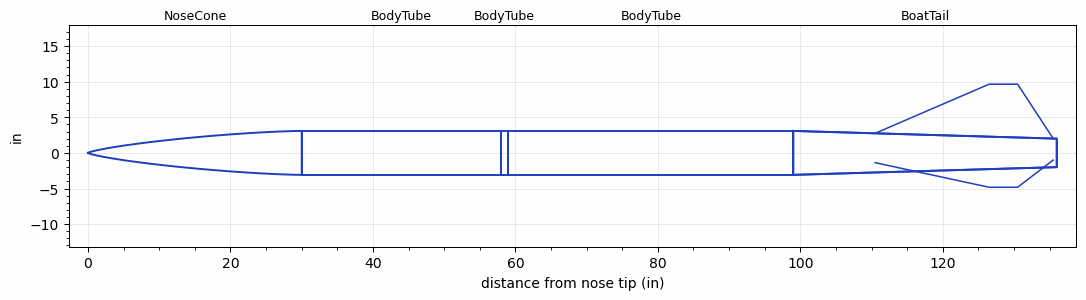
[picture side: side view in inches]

<RASAeroDocument>
 <FileVersion>2</FileVersion>
 <RocketDesign>
  <NoseCone>
   <Length>29.9999</Length>
   <Diameter>6.17</Diameter>
   <Shape>Von Karman Ogive</Shape>
   <Location>0</Location>
  </NoseCone>
  <BodyTube>
   <Length>27.9999</Length>
   <Diameter>6.17</Diameter>
   <Location>29.9999</Location>
  </BodyTube>
  <BodyTube>
   <Length>1</Length>
   <Diameter>6.17</Diameter>
   <Location>57.9998</Location>
  </BodyTube>
  <BodyTube>
   <Length>39.9999</Length>
   <Diameter>6.17</Diameter>
   <RailGuideDiameter>0.63</RailGuideDiameter>
   <RailGuideHeight>0.44</RailGuideHeight>
   <Location>58.9998</Location>
   <BoattailLength>36.9999</BoattailLength>
   <BoattailRearDiameter>4</BoattailRearDiameter>
  </BodyTube>
  <BoatTail>
   <Length>36.9999</Length>
   <Diameter>6.17</Diameter>
   <RearDiameter>4</RearDiameter>
   <Location>98.9997</Location>
   <Fin>
    <Count>3</Count>
    <Chord>25</Chord>
    <Span>6.9</Span>
    <SweepDistance>16</SweepDistance>
    <TipChord>4</TipChord>
    <Thickness>0.3125</Thickness>
    <Location>25.5</Location>
    <AirfoilSection>Hexagonal</AirfoilSection>
    <FX1>1</FX1>
    <FX3>1</FX3>
   </Fin>
  </BoatTail>
  <Surface>Smooth Paint</Surface>
  <ModifiedBarrowman>False</ModifiedBarrowman>
  <Turbulence>False</Turbulence>
  <UseBooster1>False</UseBooster1>
  <UseBooster2>False</UseBooster2>
 </RocketDesign>
 <LaunchSite>
  <Altitude>4595</Altitude>
  <Pressure>30.09</Pressure>
  <RodAngle>0</RodAngle>
  <RodLength>17</RodLength>
  <Temperature>100</Temperature>
  <WindSpeed>10</WindSpeed>
 </LaunchSite>
 <Recovery>
  <Altitude1>656.168</Altitude1>
  <Altitude2>1000</Altitude2>
  <DeviceType1>Parachute</DeviceType1>
  <DeviceType2>Parachute</DeviceType2>
  <Event1>True</Event1>
  <Event2>True</Event2>
  <Size1>24</Size1>
  <Size2>143.9997</Size2>
  <EventType1>Apogee</EventType1>
  <EventType2>Altitude</EventType2>
  <CD1>1.5</CD1>
  <CD2>2.2</CD2>
 </Recovery>
 <SimulationList>
  <Simulation>
   <SustainerEngine>O5500X  (AT)</SustainerEngine>
   <SustainerLaunchWt>85.4</SustainerLaunchWt>
   <SustainerNozzleDiameter>3.5</SustainerNozzleDiameter>
   <SustainerCG>89.4</SustainerCG>
   <SustainerIgnitionDelay>0</SustainerIgnitionDelay>
   <Booster1SeparationDelay>0</Booster1SeparationDelay>
   <Booster1IgnitionDelay>0</Booster1IgnitionDelay>
   <IncludeBooster1>False</IncludeBooster1>
   <Booster2Delay>0</Booster2Delay>
   <IncludeBooster2>False</IncludeBooster2>
   <TimetoApogee>39.56937</TimetoApogee>
   <MaxAltitude>28739.01</MaxAltitude>
   <MaxVelocity>1820.59</MaxVelocity>
   <OptimumWt>48.56063</OptimumWt>
   <OptimumMaxAlt>48.56063</OptimumMaxAlt>
  </Simulation>
  <Simulation>
   <SustainerEngine>O5500X  (AT)</SustainerEngine>
   <SustainerLaunchWt>78.1</SustainerLaunchWt>
   <SustainerNozzleDiameter>3.5</SustainerNozzleDiameter>
   <SustainerCG>89.36</SustainerCG>
   <SustainerIgnitionDelay>0</SustainerIgnitionDelay>
   <Booster1SeparationDelay>0</Booster1SeparationDelay>
   <Booster1IgnitionDelay>0</Booster1IgnitionDelay>
   <IncludeBooster1>False</IncludeBooster1>
   <Booster2Delay>0</Booster2Delay>
   <IncludeBooster2>False</IncludeBooster2>
   <TimetoApogee>39.48938</TimetoApogee>
   <MaxAltitude>29788.97</MaxAltitude>
   <MaxVelocity>1987.732</MaxVelocity>
   <OptimumWt>48.81251</OptimumWt>
   <OptimumMaxAlt>48.81251</OptimumMaxAlt>
  </Simulation>
  <Simulation>
   <SustainerEngine>O5500X  (AT)</SustainerEngine>
   <SustainerLaunchWt>76.1</SustainerLaunchWt>
   <SustainerNozzleDiameter>3.5</SustainerNozzleDiameter>
   <SustainerCG>90.67</SustainerCG>
   <SustainerIgnitionDelay>0</SustainerIgnitionDelay>
   <Booster1SeparationDelay>0</Booster1SeparationDelay>
   <Booster1IgnitionDelay>0</Booster1IgnitionDelay>
   <IncludeBooster1>False</IncludeBooster1>
   <Booster2Delay>0</Booster2Delay>
   <IncludeBooster2>False</IncludeBooster2>
   <TimetoApogee>39.64935</TimetoApogee>
   <MaxAltitude>30370.34</MaxAltitude>
   <MaxVelocity>2043.152</MaxVelocity>
   <OptimumWt>48.51375</OptimumWt>
   <OptimumMaxAlt>48.51375</OptimumMaxAlt>
  </Simulation>
  <Simulation>
   <SustainerEngine>O5500X  (AT)</SustainerEngine>
   <SustainerLaunchWt>77.5</SustainerLaunchWt>
   <SustainerNozzleDiameter>3.5</SustainerNozzleDiameter>
   <SustainerCG>89.72</SustainerCG>
   <SustainerIgnitionDelay>0</SustainerIgnitionDelay>
   <Booster1SeparationDelay>0</Booster1SeparationDelay>
   <Booster1IgnitionDelay>0</Booster1IgnitionDelay>
   <IncludeBooster1>False</IncludeBooster1>
   <Booster2Delay>0</Booster2Delay>
   <IncludeBooster2>False</IncludeBooster2>
   <TimetoApogee>39.53937</TimetoApogee>
   <MaxAltitude>29962.88</MaxAltitude>
   <MaxVelocity>2004.056</MaxVelocity>
  </Simulation>
 </SimulationList>
</RASAeroDocument>
